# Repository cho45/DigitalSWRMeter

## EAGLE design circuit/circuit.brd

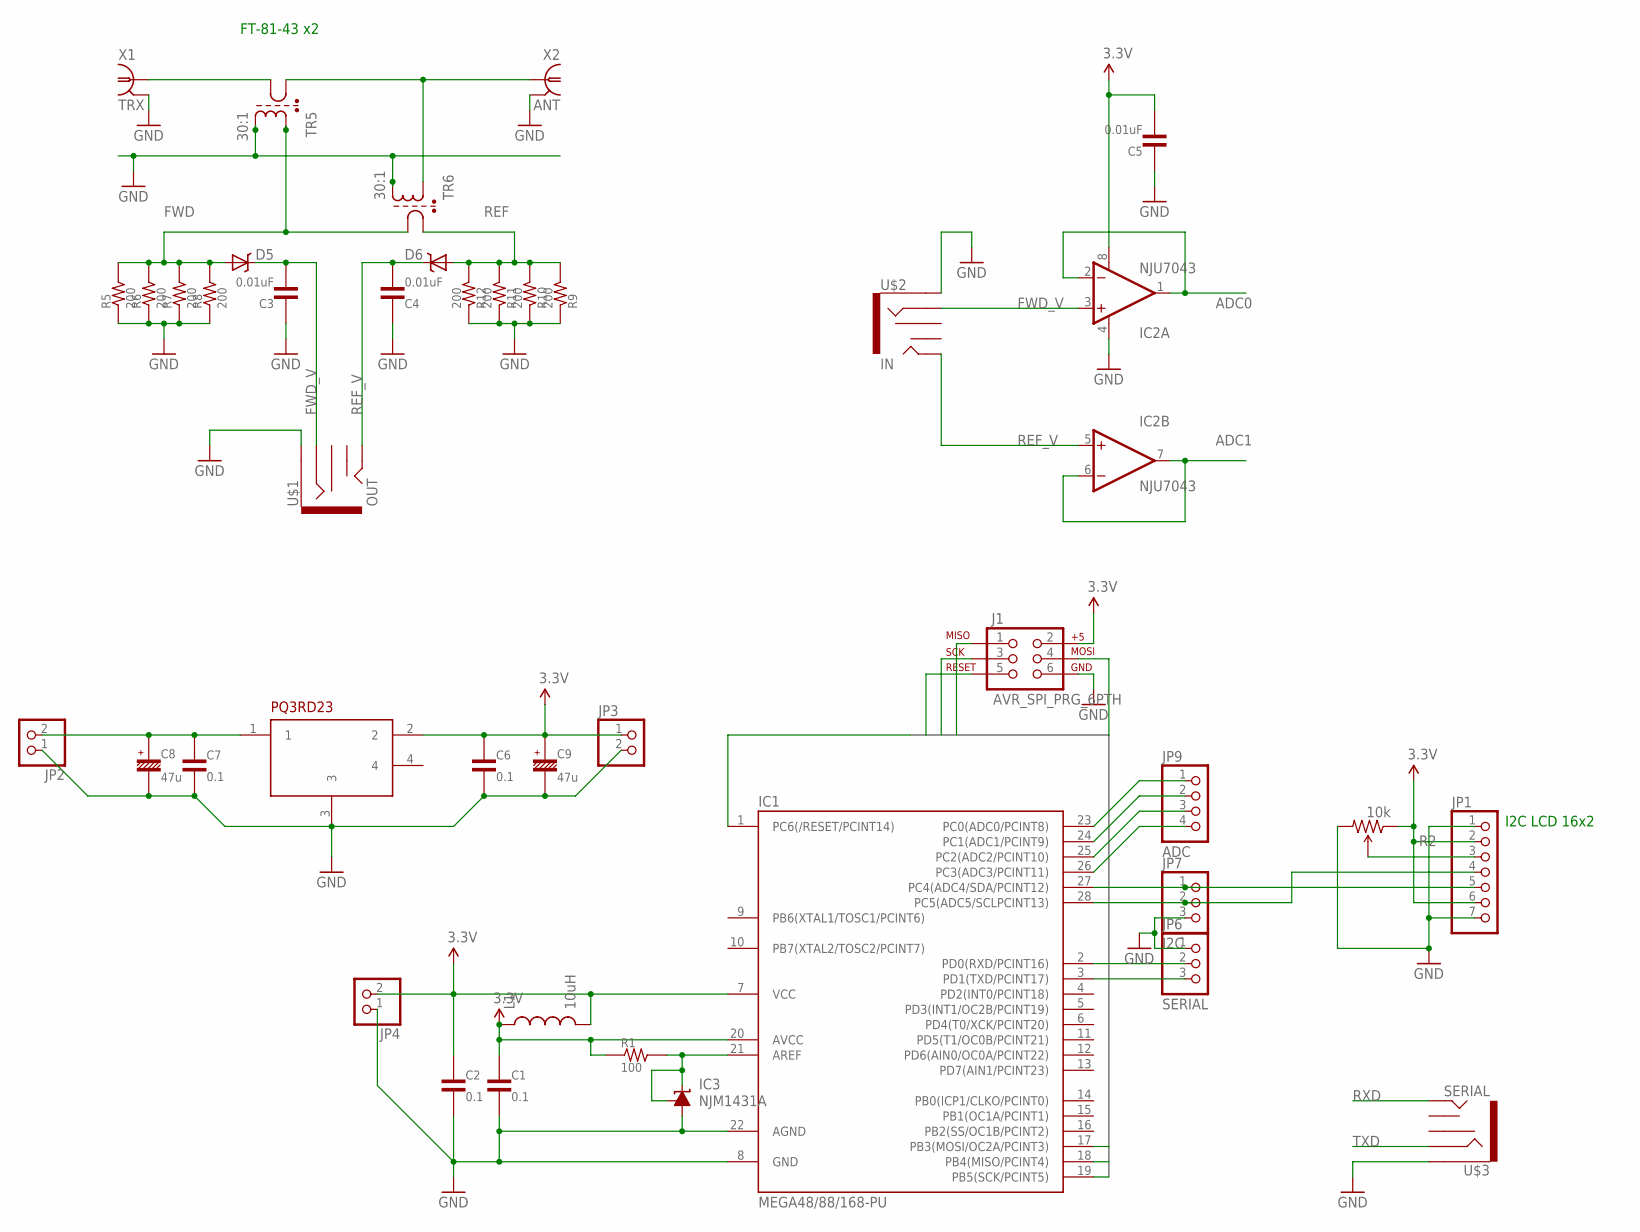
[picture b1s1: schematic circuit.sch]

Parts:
C1: 0.1; 50-0302-5.08
C2, C6, C7: 0.1; 50-0302-2.54
C3, C4, C5: 0.01uF; 50-0302-2.54
C8, C9: 47u; 16V-4-2.54
D5, D6: B340A; SMA-DIODE
IC1: MEGA48/88/168-PU; DIL28-3
IC2: NJU7043; DIP08
IC3: NJM1431A; TO-92
J1: AVR_SPI_PRG_6PTH; 2X3
JP1: PINHD-1X7; 1X07
JP2, JP3, JP4: PINHD-1X2; 1X02
JP6: SERIAL; 1X03
JP7: I2C; 1X03
JP9: ADC; 1X04
L1: 10uH; AXIAL-0.6
PQ3RD23: PQ3RD23; TO-220-4
R1: 100; 1/4W-5.08V
R2: 10k; TRIM_POT_PTH
R5, R6, R7, R8, R9, R10, R11, R12: 200; 1/4W-7.62H
TR5, TR6: 30:1; SM-R6
U$1: OUT; AUDIO-JACK-3.5MM-SMD
U$2: IN; AUDIO-JACK-3.5MM-SMD
U$3: SERIAL; AUDIO-JACK-3.5MM-SMD
X1: TRX; R141426
X2: ANT; R141426

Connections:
3.3V: C1.PAD1 (1), C2.PAD1 (1), C5.PAD2 (2), C6.PAD1 (1), C9.+, IC1.7 (VCC), IC1.20 (AVCC), IC2.8 (V+), J1.2, JP1.2, JP1.6, JP3.1, JP4.2, L1.P$1 (1), L1.P$2 (2), PQ3RD23.2, R1.PAD1 (1), R2.1 (CCW)
ADC0: IC1.23 (PC0(ADC0/PCINT8)), IC2.1 (OUT), IC2.2 (-IN), JP9.1
ADC1: IC1.24 (PC1(ADC1/PCINT9)), IC2.6 (-IN), IC2.7 (OUT), JP9.2
FWD: D5.A, R5.PAD2 (2), R6.PAD2 (2), R7.PAD2 (2), R8.PAD2 (2), TR5.5 (8), TR6.3 (4)
FWD1: D6.A, R9.PAD2 (2), R10.PAD2 (2), R11.PAD2 (2), R12.PAD2 (2)
FWD_V: C3.PAD2 (2), D5.C, IC2.3 (+IN), U$1.RING, U$2.RING
GND: C1.PAD2 (2), C2.PAD2 (2), C3.PAD1 (1), C4.PAD1 (1), C5.PAD1 (1), C6.PAD2 (2), C7.PAD2 (2), C8.-, C9.-, IC1.8 (GND), IC1.22 (AGND), IC2.4 (V-), IC3.2 (A), J1.6, JP1.1, JP1.7, JP2.1, JP3.2, JP4.1, JP6.1, JP7.3, PQ3RD23.3, R2.3 (CW), R5.PAD1 (1), R6.PAD1 (1), R7.PAD1 (1), R8.PAD1 (1), R9.PAD1 (1), R10.PAD1 (1), R11.PAD1 (1), R12.PAD1 (1), TR5.4 (5), TR6.4 (5), U$1.SLEEVE, U$2.SLEEVE, U$3.SLEEVE, X1.2, X1.3 (2), X1.4 (2), X1.5 (2), X2.2, X2.3 (2), X2.4 (2), X2.5 (2)
MISO: IC1.18 (PB4(MISO/PCINT4)), J1.1
MOSI: IC1.17 (PB3(MOSI/OC2A/PCINT3)), J1.4
unnamed: IC1.21 (AREF), IC3.1 (FB), IC3.3 (C), R1.PAD2 (2)
unnamed: C7.PAD1 (1), C8.+, JP2.2, PQ3RD23.1
unnamed: JP1.3, R2.2 (WIPER)
unnamed: IC1.27 (PC4(ADC4/SDA/PCINT12)), JP1.5, JP7.1
unnamed: IC1.3 (PD1(TXD/PCINT17)), JP6.3
unnamed: IC1.2 (PD0(RXD/PCINT16)), JP6.2
unnamed: IC1.28 (PC5(ADC5/SCLPCINT13)), JP1.4, JP7.2
unnamed: IC1.25 (PC2(ADC2/PCINT10)), JP9.3
unnamed: IC1.26 (PC3(ADC3/PCINT11)), JP9.4
unnamed: TR5.3 (4), X1.1
unnamed: TR5.1, TR6.5 (8), X2.1
REF: TR6.1
REF_V: C4.PAD2 (2), D6.C, IC2.5 (+IN), U$1.TIP, U$2.TIP
RESET: IC1.1 (PC6(/RESET/PCINT14)), J1.5
RXD: U$3.TIP
SCK: IC1.19 (PB5(SCK/PCINT5)), J1.3
TXD: U$3.RING

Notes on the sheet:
I2C LCD 16x2
FT-81-43 x2

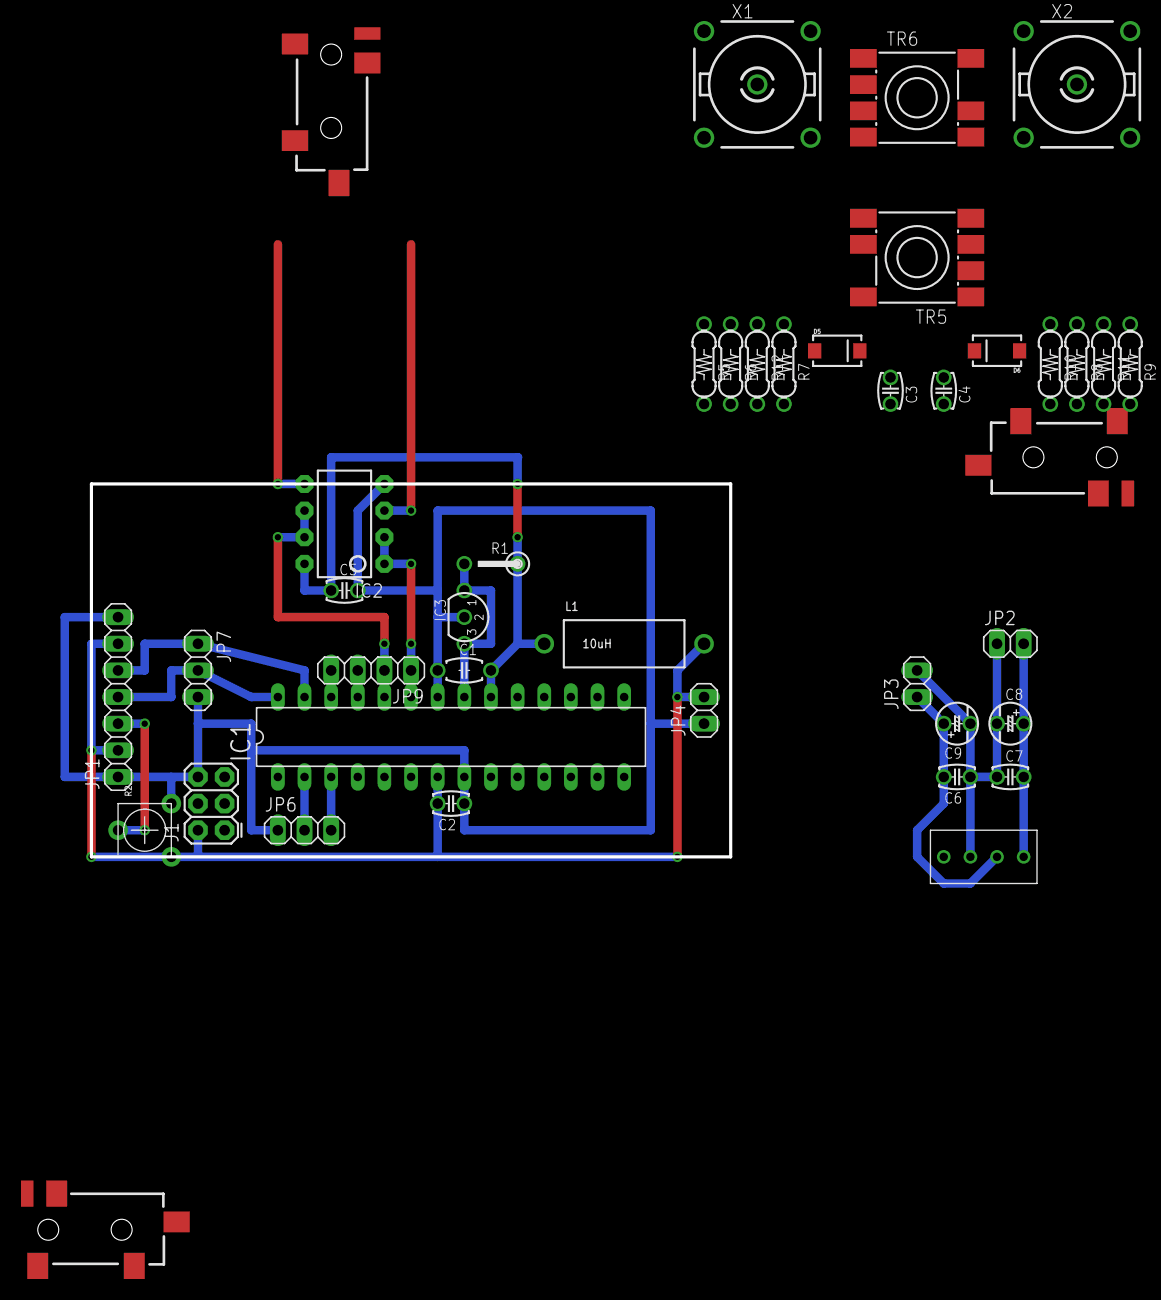
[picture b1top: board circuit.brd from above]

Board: 2 copper layers, 41 parts (0 on the bottom side), 23 nets.

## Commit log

2014-11-11 init

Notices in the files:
parts and their libraries:
SparkFun-DiscreteSemi: Licensing: CC v3.0 Share-Alike You are welcome to use this library for commercial purposes.
